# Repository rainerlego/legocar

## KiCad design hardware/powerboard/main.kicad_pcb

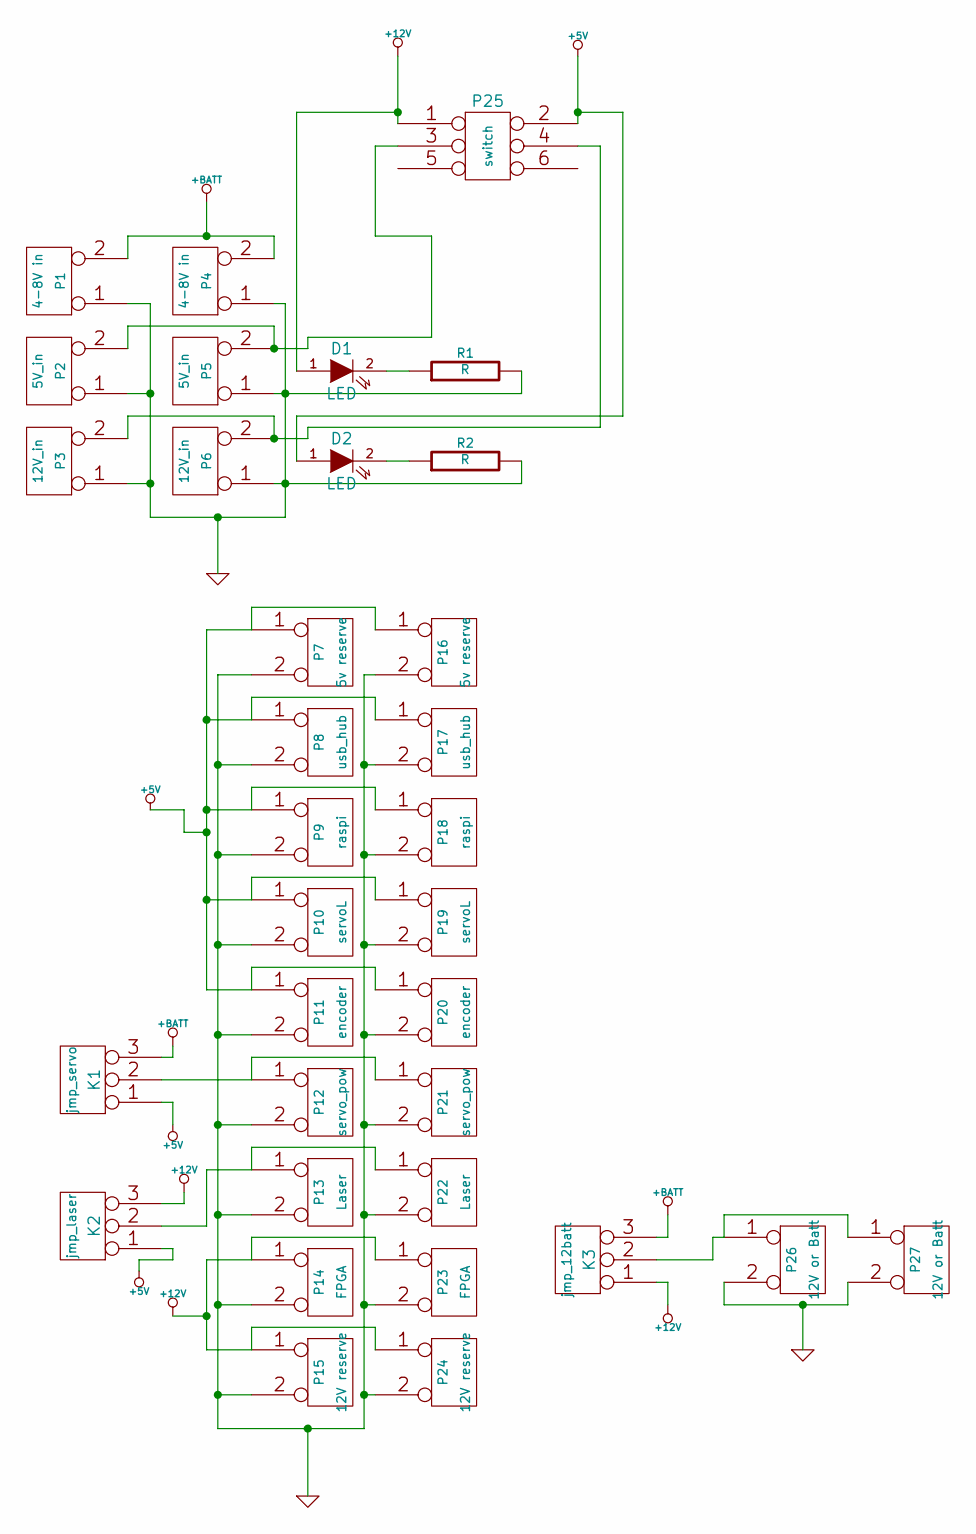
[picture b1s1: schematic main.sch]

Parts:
D1, D2: LED
K1: jmp_servo
K2: jmp_laser
K3: jmp_12batt
P1, P4: 4-8V in
P2, P5: 5V_in
P3, P6: 12V_in
P7, P16: 5v reserve
P8, P17: usb_hub
P9, P18: raspi
P10, P19: servoL
P11, P20: encoder
P12, P21: servo_pow
P13, P22: Laser
P14, P23: FPGA
P15, P24: 12V reserve
P25: switch
P26, P27: 12V or Batt
R1, R2: R

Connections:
+5V: D2.1 (A), K1.1, K2.1, P7.1, P8.1, P9.1, P10.1, P11.1, P16.1, P17.1, P18.1, P19.1, P20.1, P25.2
+12V: D1.1 (A), K2.3, K3.1, P14.1, P15.1, P23.1, P24.1, P25.1
+BATT: K1.3, K3.3, P1.2 (PM), P4.2 (PM)
GND: P1.1, P2.1, P3.1, P4.1, P5.1, P6.1, P7.2 (PM), P8.2 (PM), P9.2 (PM), P10.2 (PM), P11.2 (PM), P12.2 (PM), P13.2 (PM), P14.2 (PM), P15.2 (PM), P16.2 (PM), P17.2 (PM), P18.2 (PM), P19.2 (PM), P20.2 (PM), P21.2 (PM), P22.2 (PM), P23.2 (PM), P24.2 (PM), P26.2 (PM), P27.2 (PM), R1.2, R2.2
unnamed: P2.2 (PM), P5.2 (PM), P25.3
unnamed: P3.2 (PM), P6.2 (PM), P25.4
unnamed: K3.2 (PM), P26.1, P27.1
unnamed: D2.2 (K), R2.1
unnamed: D1.2 (K), R1.1
unnamed: K2.2 (PM), P13.1, P22.1
unnamed: K1.2 (PM), P12.1, P21.1

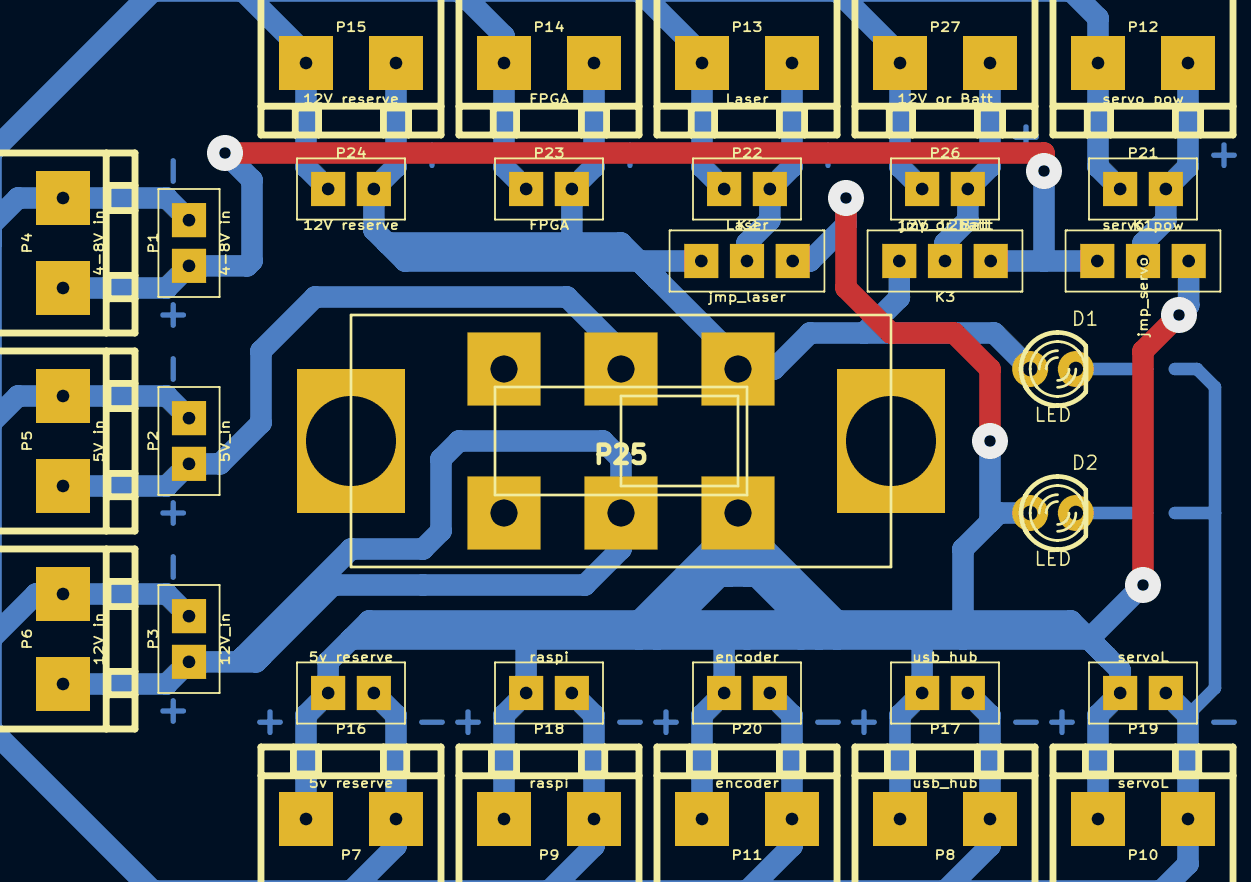
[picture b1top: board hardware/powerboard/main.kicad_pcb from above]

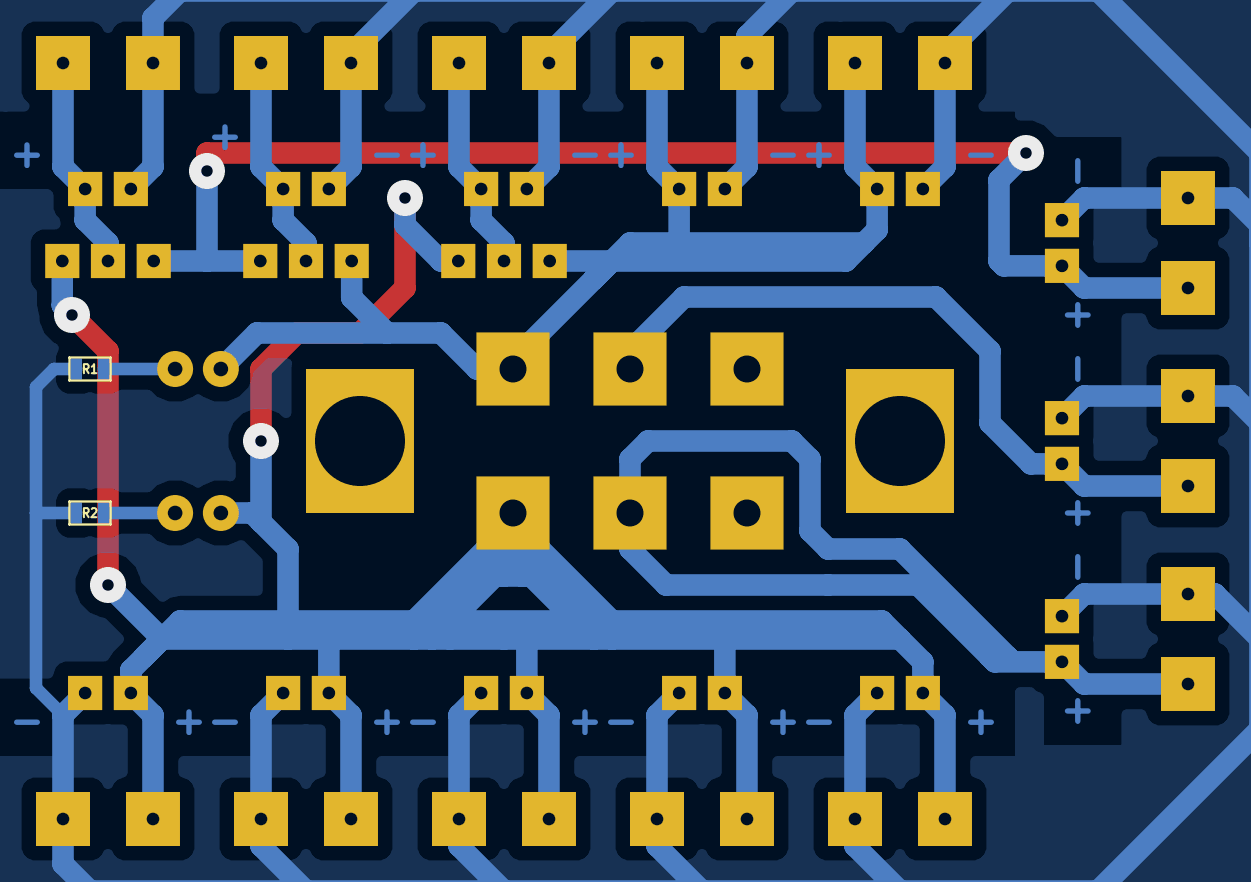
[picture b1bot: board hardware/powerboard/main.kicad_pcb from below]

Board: 2 copper layers, 34 parts (2 on the bottom side), 11 nets.

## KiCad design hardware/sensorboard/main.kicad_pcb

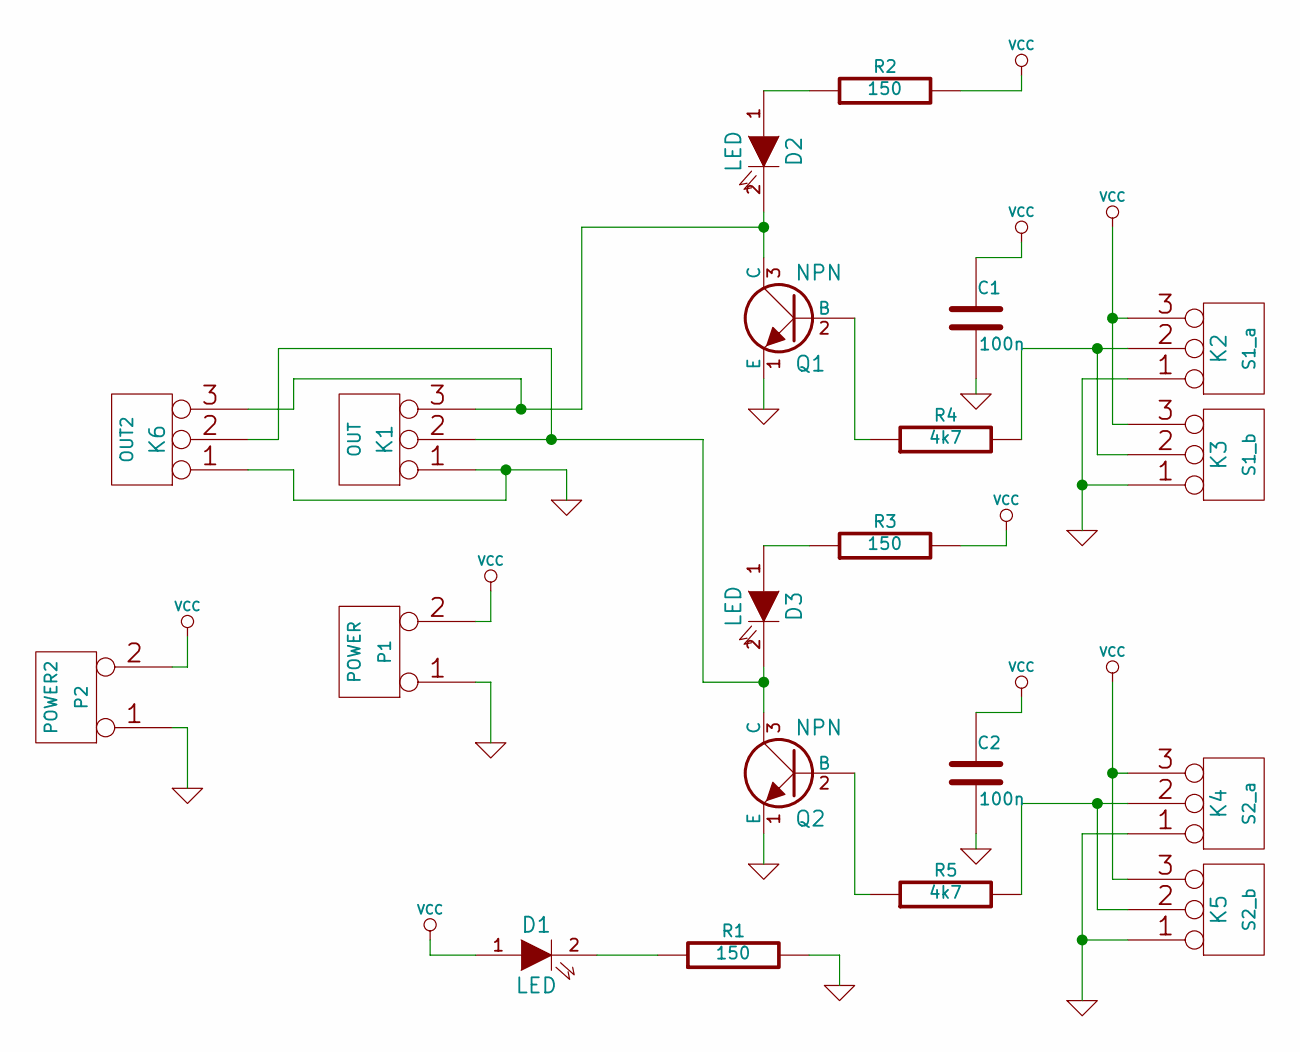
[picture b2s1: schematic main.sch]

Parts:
C1, C2: 100n
D1, D2, D3: LED
K1: OUT
K2: S1_a
K3: S1_b
K4: S2_a
K5: S2_b
K6: OUT2
P1: POWER
P2: POWER2
Q1, Q2: NPN
R1, R2, R3: 150
R4, R5: 4k7

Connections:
GND: C1.2, C2.2, K1.1, K2.1, K3.1, K4.1, K5.1, K6.1, P1.1, P2.1, Q1.1 (E), Q2.1 (E), R1.2
unnamed: D2.2 (K), K1.3, K6.3, Q1.3 (C)
unnamed: D1.2 (K), R1.1
unnamed: Q1.2 (B), R4.1
unnamed: D2.1 (A), R2.1
unnamed: Q2.2 (B), R5.1
unnamed: K2.2 (PM), K3.2 (PM), R4.2
unnamed: K4.2 (PM), K5.2 (PM), R5.2
unnamed: D3.2 (K), K1.2 (PM), K6.2 (PM), Q2.3 (C)
unnamed: D3.1 (A), R3.1
VCC: C1.1, C2.1, D1.1 (A), K2.3, K3.3, K4.3, K5.3, P1.2 (PM), P2.2 (PM), R2.2, R3.2

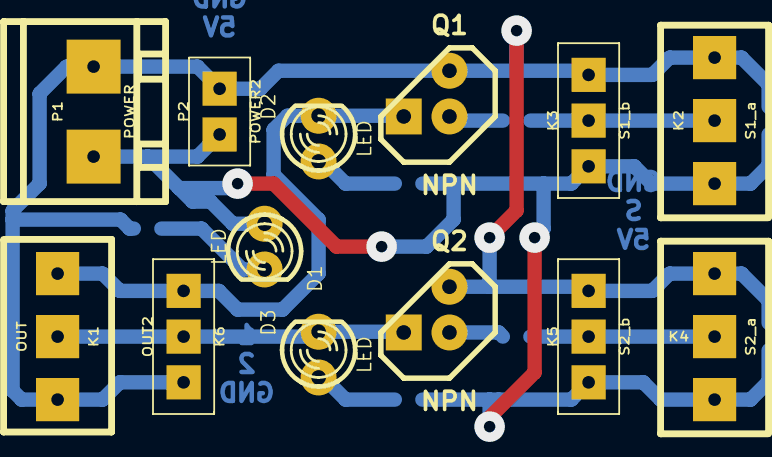
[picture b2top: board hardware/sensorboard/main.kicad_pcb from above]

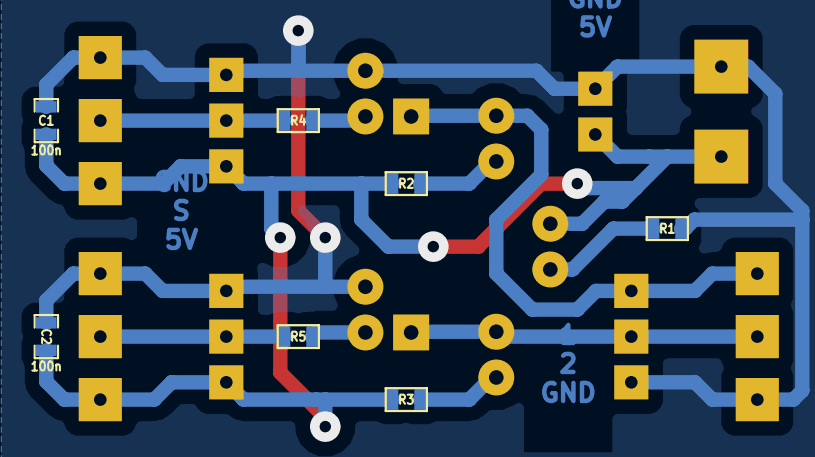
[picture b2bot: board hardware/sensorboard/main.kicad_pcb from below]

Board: 2 copper layers, 20 parts (7 on the bottom side), 11 nets.

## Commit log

2013-04-17 test
2013-04-17 manual bla
2013-04-17 env: add christian's notebook
2013-04-17 Add wenwen's repo
2013-04-18 herausgefunden wie man nios2 flashen kann
2013-04-18 nios terminal entdeckt
2013-04-18 aufgeraeumt + documentation updated
2013-04-18 initial commit cli documentation
2013-04-18 Git anleitung geschrieben
2013-04-18 gitignore
2013-04-18 gitignore updated
2013-04-18 hello world software and hardware working
2013-04-18 script for setting the PATH environment variable
2013-04-18 altera installation documentation
2013-04-18 compiling
2013-04-18 environment script updated
2013-04-19 compiling documented
2013-04-20 cleanup readme
2013-04-20 anton
2013-04-20 nios2 commandline documentation
2013-04-20 mehr doku
2013-04-20 don't ignore settings.bsp
2013-04-20 generate software makefiles from commandline
2013-04-20 ignore *.d *.exe
2013-04-20 ignore .rpt (logging-stuff)
2013-04-20 kleines board: increase on-fpga-memory
2013-04-20 hardware fuer fettes board
2013-04-20 nochmal gitignore
2013-04-22 Added my own remote
2013-04-22 julian's repo
2013-04-23 doc + remotes
2013-04-29 Android UDP/TCP Test
2013-04-30 reordered and linux socket test (for actual testing of android sockets))
2013-04-30 hardware design
2013-05-01 servo treiber schaltplan
2013-05-01 board angefangen
2013-05-01 layout
2013-05-01 routing angefangen bugs fixed
2013-05-01 Software design teil hingefügt
2013-05-01 board servo fertig routed
2013-05-01 fixed board mirror error
2013-05-01 servoboard: den verdammten programmieradapter verschoben
2013-05-02 servoboard zone fix
2013-05-07 servoboard - 7805 integration
2013-05-07 servoboard firmware angefangen
2013-05-07 servoboard firmware: twi protocol
2013-05-08 servoboard: firmware nahezu fertig
2013-05-08 servoboard: firmware: fixme comment
2013-05-08 servoboard: firmware zeuch
2013-05-08 servoboard: firmware: protocol description
2013-05-08 servoboard: firmware: ledfix, documentation, ...
2013-05-08 servoboard: firmware: code aufgeräumt linked nicht mehr :(
2013-05-08 servoboard:firmware: solved linking problem
2013-05-08 servoboard: firmware: fixed all warnings
2013-05-08 twi: statemachine aufgeraumt
2013-05-13 fix twi interrupt clear
2013-05-13 twi fix twi int
2013-05-13 daten können verschickt werden (es gibt nur noch keine daten)
2013-05-13 servoboard: code aufgeräumt
2013-05-13 receive commands
2013-05-13 servoboard: fixed memoryleak
2013-05-13 servoboard: TWI protocol description
2013-05-15 Fixed overflow bug in twi.c
2013-05-15 servoboard: fix servoNr
2013-05-15 raspi: first servoboard interface
2013-05-15 raspi: changed adress servo board
2013-05-15 raspi: servoboard-treiber (blind) aufgeräumt. compiled zumindest
2013-05-15 wiimote: auch komplett blind und ungetestet
2013-05-15 servoboard: twi: leds 'verbessert'
2013-05-15 servoboard: twi: leds: klammern
2013-05-15 raspi: combined tcp server and wiimote listener
2013-05-16 testservp.py angepasst mit cli arg
2013-05-17 servoboard: led protocol fixed
2013-05-17 servoboard: pytest allow servo number
2013-05-17 servoboard: twi: minor fix + protocol documentation
2013-05-17 servoboard: firmware
2013-05-19 car simulation started
2013-05-19 sim: auto fährt :)
2013-05-19 sim: auto fährt und lässt sich steuern!!
2013-05-19 sim: clean up
2013-05-19 sim: text :)
2013-05-19 sim: esc -> reset, spacebar -> motor off
2013-05-19 sim: allow camera move/zoom
2013-05-20 sim: very simple map
2013-05-20 raspi: vorarbeit fuer simulation
2013-05-20 raspi: schnittstelle zur simulation sollte funktionieren
2013-05-20 sim: sensor angefangen
2013-05-20 raspi: connect zur simulation
2013-05-20 sim: simple 3d scanner works
2013-05-20 sim: tcpserver
2013-05-20 tcpserver integriert
2013-05-20 sim: laserscanner optimiert
2013-05-20 sim: switch between user-controlled and tcp-controlled car
2013-05-20 sim: laserscanner eyecandy
2013-05-20 sim: lenkung über tcp funktioniert
2013-05-20 sim: beschleunigung per tcp
2013-05-20 Makefile
2013-05-20 minor stuff
2013-05-20 raspi: makefile
2013-05-20 sim: invert translation servo->accel
2013-05-20 software-bildchen
2013-05-20 compile-scripts brauchen wir nicht mehr
2013-05-20 simulator: leds ;)
2013-05-20 sim: sensor fix
2013-05-20 sim: mapeditor
2013-05-20 sim: steering direction inverted
2013-05-20 Android: GUI beta
2013-05-20 Android
2013-05-20 sim: laserscanner fix: auch große objekte werden korrekt erkannt
2013-05-20 sim: control unmirror
2013-05-20 gitignore: .class, .dex
2013-05-20 Android project with build file
2013-05-20 sim: framerate = 50fps
2013-05-20 Android: Bugs fixed
2013-05-21 sim: time fix, ostacle: what you see is what car sees
2013-05-21 Changed programmer to tinyisp programmer.
2013-05-21 android: funktionierendes buildfile
2013-05-21 Changed design to show current chosen design.
2013-05-21 Android: Source files
2013-05-21 Android: new TODO
2013-05-22 raspi: wii funktioniert ;)
2013-05-22 debug-output
2013-05-22 raspi: wiimote: while(1)-loop
2013-05-22 raspi: wii: enable/disable
2013-05-23 Android new default setting
2013-05-23 Added camera datasheet Added first version of FPGA project for i2c communication.
2013-05-24 raspi: debugging
2013-05-24 moar debugging
2013-05-27 servo delay was nicht funktioniert
2013-05-27 wii: zeit-interval-hack
2013-05-27 wii: button mode
2013-05-28 servoboard: watchdog 0.5s no message -> reset servos
2013-05-28 raspi: delegate control to one controlling device
2013-05-28 Android: Bug beseitigen
2013-05-28 firmware: scope comment
2013-05-28 firmware: dummy-ping-command
2013-05-28 wii: ping eingebaut und dann doch sein lassen wegen rauschen + disconnect-problem
2013-05-29 Added optimal(!) cflags to makefile.
2013-05-29 address
2013-06-01 hardware:sensorboard
2013-06-01 sensor und powerboard + muell
2013-06-07 midterm presentation
2013-06-07 raspi: für simulation-demo hergerichtet
2013-06-09 komische änderung nach Git push
2013-06-10 Android + send getperm
2013-06-10 Praesentation changing
2013-06-10 changing presentation
2013-06-10 fixed typos
2013-06-10 Added FPGA section to documentation, removed beamer navigation icons.
2013-06-10 Added some quartus files to gitignore.
2013-06-10 dietz invert control raspi
2013-06-12 bildchen-ordner
2013-06-12 pres updated
2013-06-14 added ros packages
2013-06-15 Added testbench for i2c_master component.
2013-06-15 Added first version of i2ctest component. Implemented state machine to set speed of servo 0.
2013-06-17 Updated i2ctest code from website. Sending multi-byte commands now works. W
2013-06-24 - Added first version of speed sensor with associated testbench. - Used the edge detector in i2c_test.vhd
2013-06-26 spi vhdl
2013-06-26 spi: fixed data size
2013-06-26 spi: read/write buffer
2013-06-26 spi simulation
2013-06-26 spi: fix miso
2013-06-27 spi: complete bit
2013-06-27 Removed division by 4.
2013-06-27 - Fixed errors in spi and its test bench.
2013-06-27 - Moved motor controller. - Correctly implemented SPI. First 8 bits sent to master from SPI controller can are always zero.
2013-06-28 - Fixed some bugs in motor controller (busy_count was not being reset) - Added toplevel file for programming the FPGA - Added test bench for toplevel.
2013-07-01 Added raspi to fpga spi interface
2013-07-01 - Fixed some bugs in the busy/enabled/reset_n handling logic of the motor controller.
2013-07-03 - Added Debounce timer to toplevel. - Still problems with state machine in motor controller. I suspect it is because of changing clock domains between the i2c master and the motor controller. - Moved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
2013-07-03 - Renamed motor controller test - Corrected implementation. Simulation is now correct (last argument was lost). Also converted to two-process state machine form.
2013-07-08 raspi: spi
2013-07-08 - Added falling edge detection to edge_detector. - Fixed endianness issue with the motor controller. - Working version!
2013-07-08 spi sync auf clk_50
2013-07-08 double
2013-07-09 added final presi draft
2013-07-10 spi working 2 bytes delay
2013-07-10 raspi: spi: tcpserver
2013-07-10 raspi: spi zeuch
2013-07-10 spi files (unstable)
2013-07-10 spi defunct
2013-07-10 Added conversion of speed for fpga
2013-07-10 Fixed speed conversion
2013-07-10 - Corrected speed sensor to use 1/clock cycles measure for rotation
2013-07-10 - Implemented speed control and toplevel component for it for testing.
2013-07-10 spi running again no delay but transmission erroer random
2013-07-14 Added seven-segment debugging output of current speed.
2013-07-15 - Fixed some typos, added Pi communication with FPGA
2013-07-15 die finaldie final
2013-08-02 douk
2013-08-02 doku
2013-08-06 fpga: comments
2013-08-06 i2ctest.qsf
2013-08-06 move raspi folder
2013-08-06 move raspi2
2013-08-06 spitest debug
2013-08-06 asda
2013-08-06 pin assignements
2013-08-06 fpga spireader
2013-08-06 spi fixed bit shift send+receive works now
2013-08-06 spireader: no edge-detect
2013-08-06 fpga spireader geht n bisschen
2013-08-06 fpga: spireader state machine, ungetestet
2013-08-07 spi fix state loss
2013-08-07 fpga: spireader
2013-08-07 spi syntax error '' fix
2013-08-07 fpga spireader debugpin
2013-08-07 spi fix try
2013-08-07 debig pin spi
2013-08-07 assign
2013-08-07 raspi: speed/acc-switch
2013-08-07 raspi: fix
2013-08-07 raspi: preambeln
2013-08-07 spi smooth clock
2013-08-07 smooth edge detector
2013-08-07 fpga: servo controller
2013-08-07 spireader: mehr debugleds
2013-08-07 fpga some project file
2013-08-07 SPI RUNNING STABLE finally!!!
2013-08-07 fpga: acc/speed-switch component + bigger toplevel
2013-08-07 fpga: noch groessere all mit speed controller und speed sensoren
2013-08-07 fpga: debug leds
2013-08-07 raspi: implement AS enable/disable command
2013-08-07 raspi: wii: implement speed/acc switch and antischlupf switch
2013-08-07 fpga: antischlupf in spireader statemachine + kabel rübergelegt zum speed_controller
2013-08-08 raspi: sollte gehn
2013-08-08 speed control alpha
2013-08-08 alle 7segment
2013-08-08 speed control
2013-08-08 stuff tl
2013-08-08 speed control compiles
2013-08-08 speedsensor 2
2013-08-08 fpga: servos getauscht + speed command
2013-08-08 fpga: speed command
2013-08-08 bsdaf
2013-08-08 fpga: speedraw command
2013-08-08 raspi: speedraw cmd
2013-08-08 servocontroller: testing für rainer
2013-08-08 raspi
2013-08-08 fix slip bug + react to enable_antischlupf
2013-08-09 speed control ;
2013-08-09 i2c: move everytihng to one statemachine and fix servo-dance
2013-08-09 raspi: debug
2013-08-09 fpga: 7segment + schneller i2c senden
2013-08-09 fpga: ka
2013-08-09 spireader: send speeds via spi
2013-08-09 stuff
2013-08-09 plots
2013-08-09 raspi: logging
2013-08-09 adjust stuff
2013-08-09 daten
2013-08-09 plots2
2013-08-10 doku style a ob besser oder nciht
2013-08-10 fixed images
2013-08-10 pics fix
2013-08-10 speed control plots
2013-08-10 learned
2013-08-10 img fail
2013-08-10 bildchen
2013-08-12 servoboard
2013-08-12 firmware
2013-08-12 blub
2013-08-13 doku speed control
2013-08-13 lessons
2013-08-13 simu
2013-08-13 -todo
2013-08-13 doku future work
2013-08-13 fpga
2013-08-13 title
2013-08-13 figure
2013-08-13 duku bla
